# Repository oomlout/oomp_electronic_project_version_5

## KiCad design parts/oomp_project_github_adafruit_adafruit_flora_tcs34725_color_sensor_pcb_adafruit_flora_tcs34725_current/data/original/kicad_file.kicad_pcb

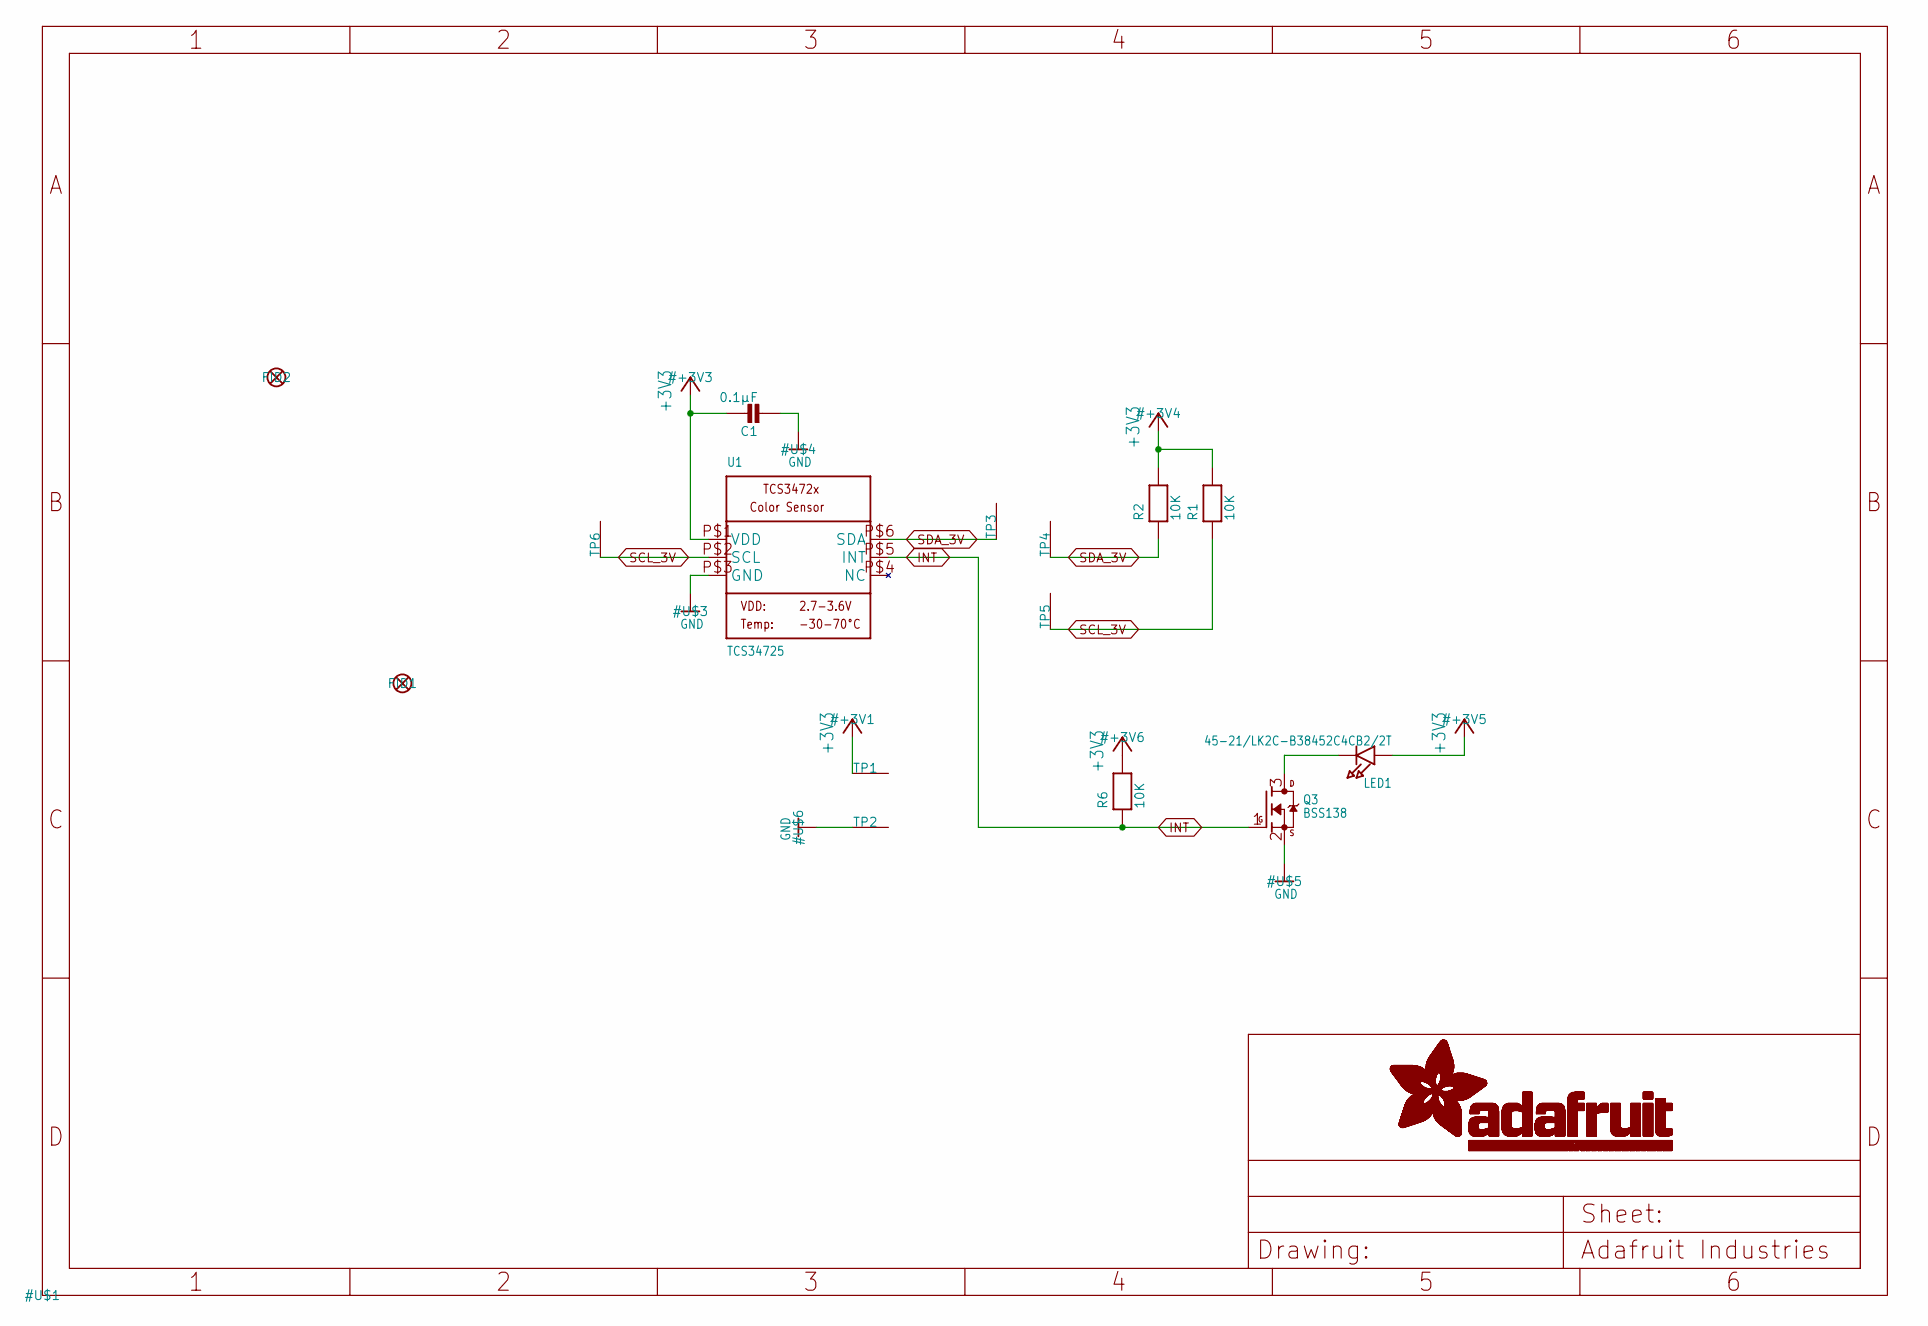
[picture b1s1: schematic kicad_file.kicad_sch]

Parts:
C1: 0.1µF; _0805
FID1, FID2: FIDUCIAL""; FIDUCIAL_1MM
LED1: 45-21/LK2C-B38452C4CB2/2T; EVERLIGHT_45-21
Q3: BSS138; SOT23-WIDE
R1, R2, R6: 10K; _0805
TP1, TP2, TP3, TP4, TP5, TP6: SEWTAP0.5IN; SEWINGTAP_0.5
U1: TCS34725; TCS3472_FN6

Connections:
+3V3: C1.1, LED1.A, R1.2, R2.2, R6.2, TP1.TAP, U1.P$1 (VDD)
GND: C1.2, Q3.2 (S), TP2.TAP, U1.P$3 (GND)
INT: Q3.1 (G), R6.1, U1.P$5 (INT)
unnamed: LED1.K (C), Q3.3 (D)
SCL_3V: R1.1, TP5.TAP, TP6.TAP, U1.P$2 (SCL)
SDA_3V: R2.1, TP3.TAP, TP4.TAP, U1.P$6 (SDA)

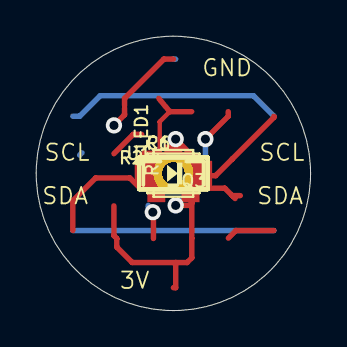
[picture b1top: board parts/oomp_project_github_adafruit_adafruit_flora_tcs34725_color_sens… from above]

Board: 2 copper layers, 15.2 x 15.2 mm, 16 parts (1 on the bottom side), 6 nets.

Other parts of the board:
U$8: ADAFRUIT_3.5MM

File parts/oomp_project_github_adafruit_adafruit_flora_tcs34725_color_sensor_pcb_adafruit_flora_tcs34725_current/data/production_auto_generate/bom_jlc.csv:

Comment,Designator,Footprint,LCSC Part #
,U$8,Adafruit Flora TCS34725-import-fps:ADAFRUIT_3.5MM,
0.1µF,C1,Adafruit Flora TCS34725-import-fps:_0805,
10K,"R1,R2,R6",Adafruit Flora TCS34725-import-fps:_0805,C17414
45-21/LK2C-B38452C4CB2/2T,LED1,Adafruit Flora TCS34725-import-fps:EVERLIGHT_45-21,
BSS138,Q3,Adafruit Flora TCS34725-import-fps:SOT23-WIDE,C52895
SEWTAP0.5IN,"TP1,TP2,TP3,TP4,TP5,TP6",Adafruit Flora TCS34725-import-fps:SEWINGTAP_0.5,
TCS34725,U1,Adafruit Flora TCS34725-import-fps:TCS3472_FN6,

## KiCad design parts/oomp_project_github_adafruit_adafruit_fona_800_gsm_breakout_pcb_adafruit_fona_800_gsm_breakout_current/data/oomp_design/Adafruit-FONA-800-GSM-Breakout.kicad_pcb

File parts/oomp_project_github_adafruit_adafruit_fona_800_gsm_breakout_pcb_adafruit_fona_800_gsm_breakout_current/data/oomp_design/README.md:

# OOMP KiCad design copy

Open `Adafruit-FONA-800-GSM-Breakout.kicad_pro` (or the `.kicad_pcb` / `.kicad_sch`) in KiCad. Local OOMP libraries are under `libraries/`. Original inputs are preserved in [../original/](../original/).

Only verified unchanged installed KiCad defaults were renamed. Modified, custom, unmatched and unavailable items remain unchanged. Soldering variants are never swapped during conversion. Existing pad coordinates, nets and UUIDs are preserved.

See [conversion_report.yaml](conversion_report.yaml) for every conversion and skip. Copy this directory before editing; regeneration refuses to overwrite edited design files.

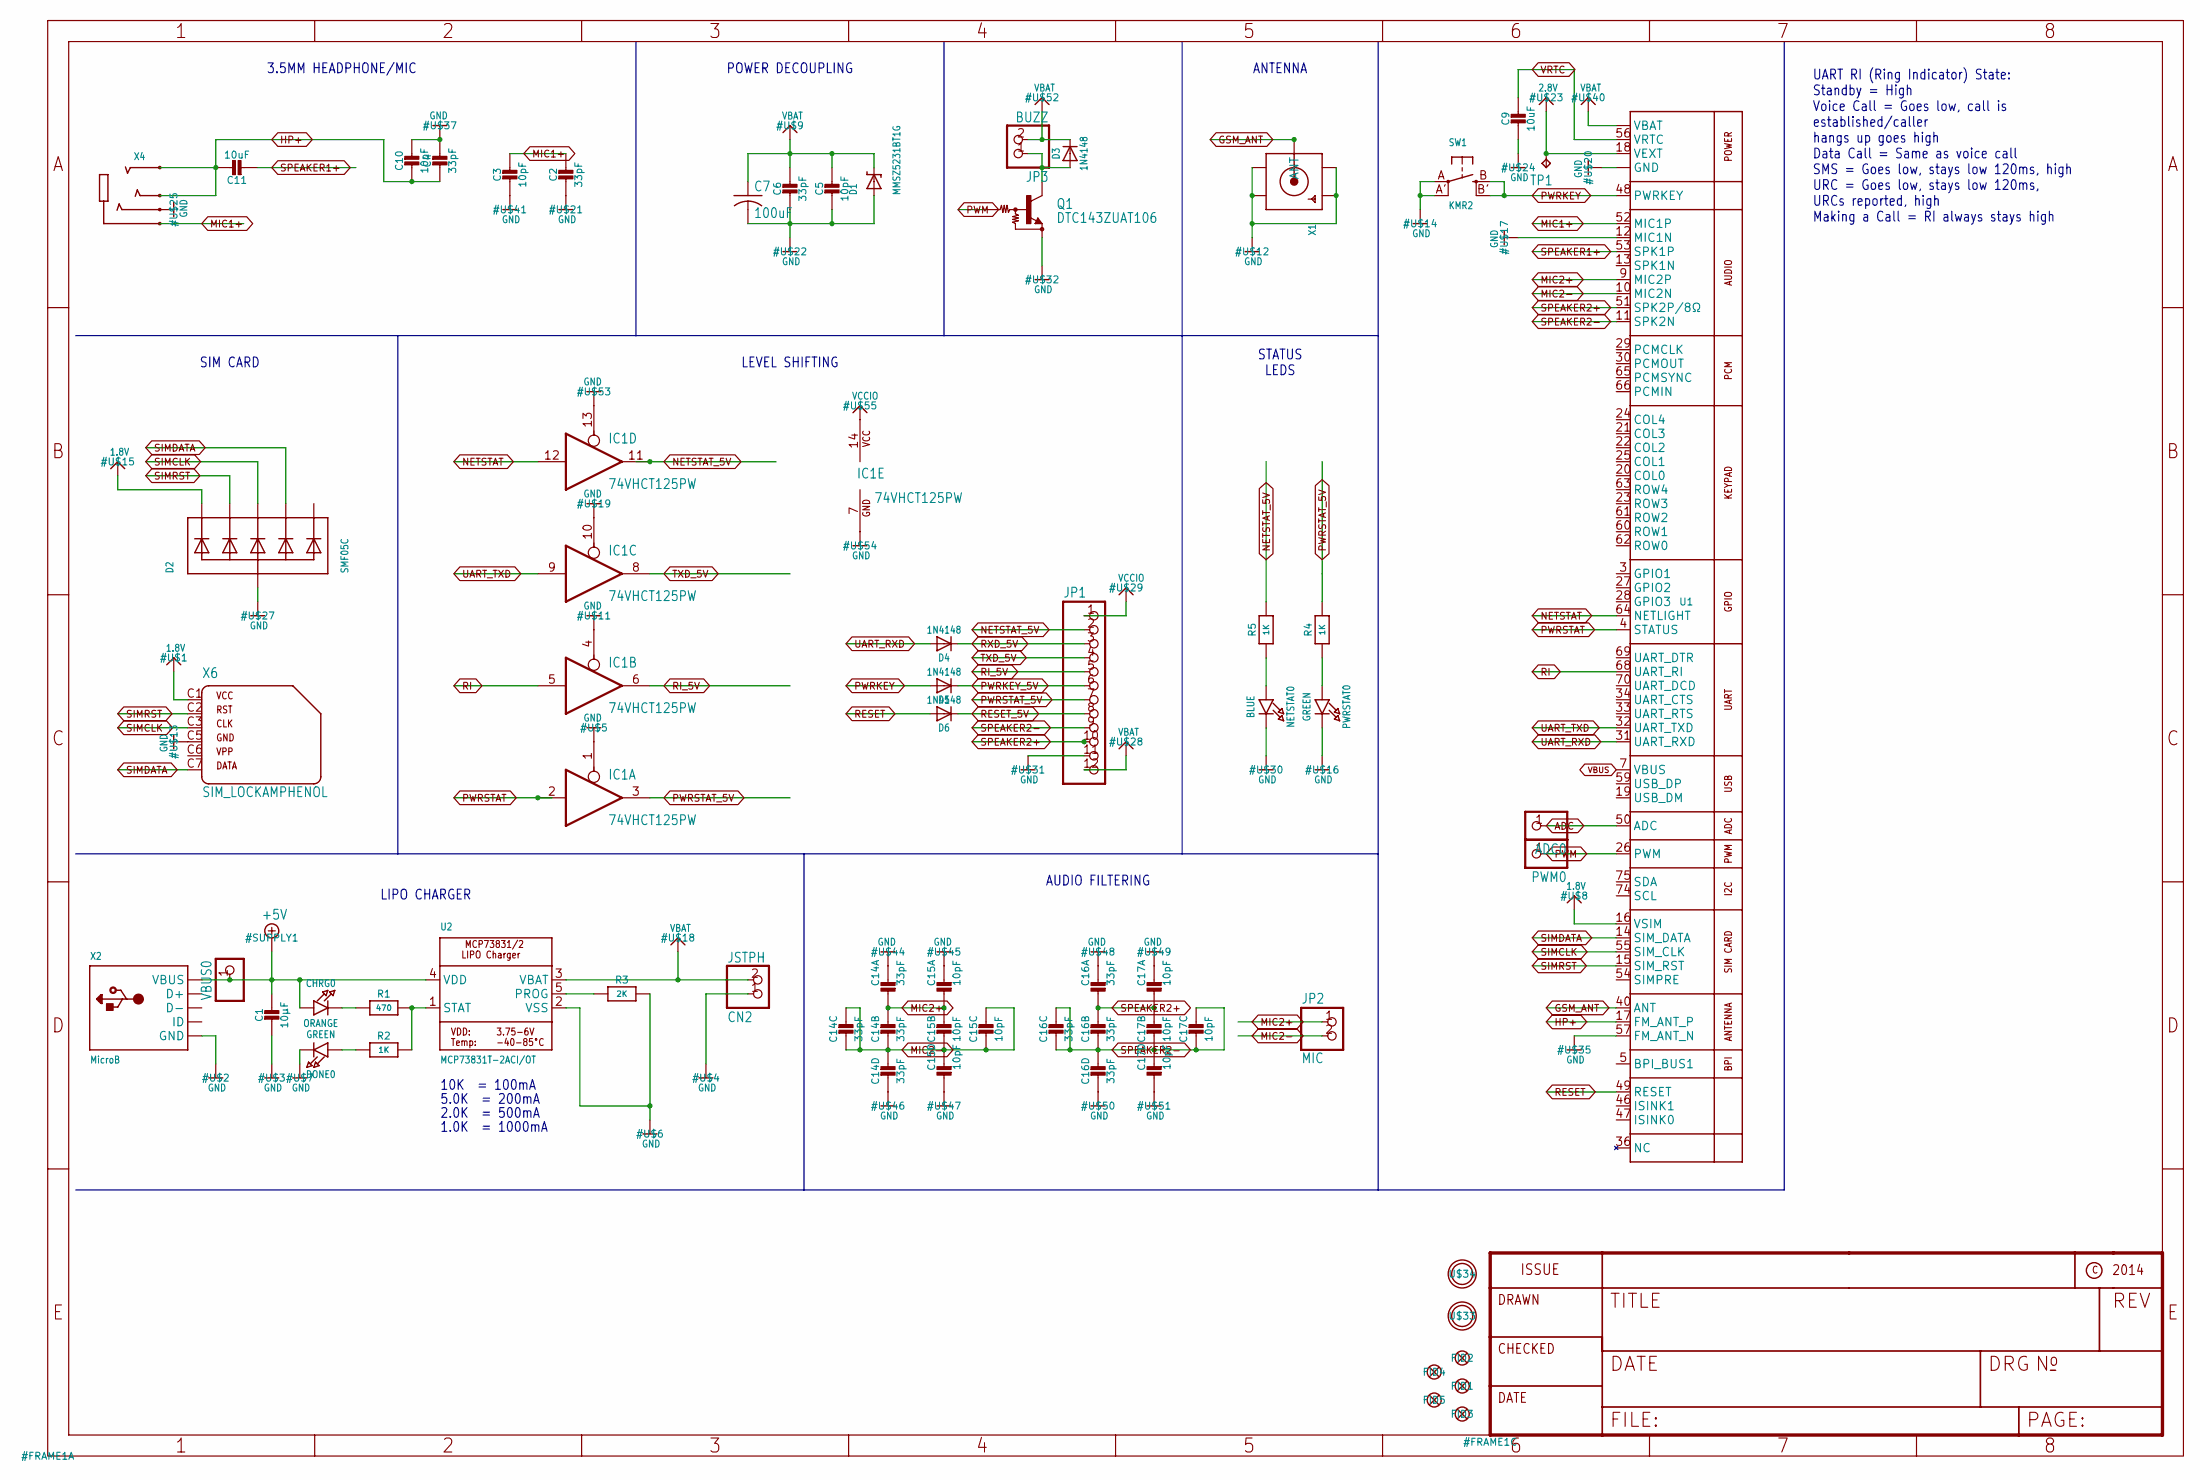
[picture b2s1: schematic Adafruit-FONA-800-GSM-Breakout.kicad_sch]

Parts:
ADC0: PINHD-1X1CB; 1X01-CLEANBIG
C1: 10µF; 0805-NO
C2, C4, C6: 33pF; 0805-NO
C3, C5, C10: 10pF; 0805-NO
C7: 100uF; C1210
C9, C11: 10uF; 0805-NO
C14, C16: 33pF; RESPACK_4X0603
C15, C17: 10pF; RESPACK_4X0603
CHRG0: ORANGE; CHIPLED_0805_NOOUTLINE
CN2: JSTPH; JSTPH2
D1: MMSZ5231BT1G; SOD-123
D2: SMF05C; SOT363
D3, D4, D5, D6: 1N4148; SOD-323
DONE0: GREEN; CHIPLED_0805_NOOUTLINE
FID1, FID2, FID3, FID4, FID5: FIDUCIAL""; FIDUCIAL_1MM
IC1: 74VHCT125PW; TSSOP14
JP1: PINHD-1X12-CB; 1X12-CB
JP2: MIC; 1X02_ROUND
JP3: BUZZ; 1X02_ROUND
NETSTAT0: BLUE; CHIPLED_0805_NOOUTLINE
PWM0: PINHD-1X1CB; 1X01-CLEANBIG
PWRSTAT0: GREEN; CHIPLED_0805_NOOUTLINE
Q1: DTC143ZUAT106; SC59-BEC
R1: 470; 0805-NO
R2, R4, R5: 1K; 0805-NO
R3: 2K; 0805-NO
SW1: KMR2; BTN_KMR2_4.6X2.8
TP1: TPTP11R; TP11R
U1: SIM800H/L; SIM800L
U2: MCP73831T-2ACI/OT; SOT23-5
U$33, U$34: MOUNTINGHOLE2.5; MOUNTINGHOLE_2.5_PLATED
VBUS0: PINHD-1X1CB; 1X01-CLEANBIG
X1: SMACONNECTOR_EDGE_UFL; SMA_EDGELAUNCH_UFL
X2: MicroB; 4UCONN_20329
X4: AUDIO_3.5MMJACK_4POL; 4UCONN_18510
X6: SIM_LOCKAMPHENOL; C707_10M006_512_2

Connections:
1.8V: D2.1 (C1), U1.16 (VSIM), X6.C1 (1)
2.8V: TP1.TP, U1.18 (VEXT)
+5V: C1.1, CHRG0.A, U2.4 (VDD), VBUS0.1, X2.VBUS
ADC: ADC0.1, U1.50 (ADC)
GND: C1.2, C2.2, C3.2, C4.1, C5.2, C6.2, C7.2, C9.2, C10.1, C14.5 (2), C14.8 (2), C15.4 (1), C15.8 (2), C16.5 (2), C16.8 (2), C17.4 (1), C17.8 (2), CN2.1, D1.A, D2.2 (A), DONE0.C, IC1.1 (OE), IC1.4 (OE), IC1.7 (GND), IC1.10 (OE), IC1.13 (OE), JP1.11, NETSTAT0.C, PWRSTAT0.C, Q1.E, R3.2, SW1.A, SW1.A' (P1), U1.2 (GND), U1.6 (GND), U1.8 (GND), U1.12 (MIC1N), U1.35 (GND), U1.37 (GND), U1.38 (GND), U1.39 (GND), U1.41 (GND), U1.43 (GND), U1.44 (GND), U1.45 (GND), U1.57 (FM_ANT_N), U1.58 (GND), U1.67 (GND), U1.71 (GND), U1.72 (GND), U1.73 (GND), U1.76 (GND), U1.77 (GND), U1.78 (GND), U1.79 (GND), U1.80 (GND), U1.81 (GND), U1.82 (GND), U1.83 (GND), U1.84 (GND), U1.85 (GND), U1.86 (GND), U1.87 (GND), U1.88 (GND), U2.2 (VSS), X1.GND@1 (GND1), X1.GND@2 (GND2), X1.GND@3 (GND3), X1.GND@4 (GND4), X2.BASE@1 (GND), X2.BASE@2 (GND), X2.GND, X2.SPRT@1 (GND), X2.SPRT@2 (GND), X2.SPRT@3 (GND), X2.SPRT@4 (GND), X4.4-INNER_SLEEVE (RING1), X6.C5 (4)
GSM_ANT: U1.40 (ANT), X1.P (ANT)
HP+: C4.2, C10.2, C11.1, U1.17 (FM_ANT_P), X4.2-TIP (RING3), X4.3-OUTER_SLEEVE (RING2)
MIC1+: C2.1, C3.1, U1.52 (MIC1P), X4.1-GND (TIP)
MIC2+: C14.1, C14.2 (1), C15.1, C15.2 (1), JP2.1, U1.9 (MIC2P)
MIC2-: C14.3 (1), C14.4 (1), C14.6 (2), C14.7 (2), C15.3 (1), C15.5 (2), C15.6 (2), C15.7 (2), JP2.2, U1.10 (MIC2N)
unnamed: CHRG0.C, R1.1
unnamed: R1.2, R2.2, U2.1 (STAT)
unnamed: PWRSTAT0.A, R4.1
unnamed: R3.1, U2.5 (PROG)
unnamed: DONE0.A, R2.1
unnamed: NETSTAT0.A, R5.1
unnamed: D3.A, JP3.1, Q1.C
NETSTAT: IC1.12 (I), U1.64 (NETLIGHT)
NETSTAT_5V: IC1.11 (O), JP1.2, R5.2
PWM: PWM0.1, Q1.B, U1.26 (PWM)
PWRKEY: D5.A, SW1.B (S), SW1.B' (S1), U1.48 (PWRKEY)
PWRKEY_5V: D5.C, JP1.6
PWRSTAT: IC1.2 (I), U1.4 (STATUS)
PWRSTAT_5V: IC1.3 (O), JP1.7, R4.2
RESET: D6.A, U1.49 (RESET)
RESET_5V: D6.C, JP1.8
RI: IC1.5 (I), U1.68 (UART_RI)
RI_5V: IC1.6 (O), JP1.5
RXD_5V: D4.C, JP1.3
SIMCLK: D2.4 (C3), U1.55 (SIM_CLK), X6.C3 (3)
SIMDATA: D2.5 (C4), U1.14 (SIM_DATA), X6.C7 (6)
SIMRST: D2.3 (C2), U1.15 (SIM_RST), X6.C2 (2)
SPEAKER1+: C11.2, U1.53 (SPK1P)
SPEAKER2+: C16.1, C16.2 (1), C17.1, C17.2 (1), JP1.10, U1.51 (SPK2P/8Ω)
SPEAKER2-: C16.3 (1), C16.4 (1), C16.6 (2), C16.7 (2), C17.3 (1), C17.5 (2), C17.6 (2), C17.7 (2), JP1.9, U1.11 (SPK2N)
TXD_5V: IC1.8 (O), JP1.4
UART_RXD: D4.A, U1.31 (UART_RXD)
UART_TXD: IC1.9 (I), U1.32 (UART_TXD)
VBAT: C5.1, C6.1, C7.1, CN2.2, D1.C, D3.C, JP1.12, JP3.2, U1.1 (VBAT), U1.42 (VBAT), U2.3 (VBAT)
VBUS: U1.7 (VBUS)
VCCIO: IC1.14 (VCC), JP1.1
VRTC: C9.1, U1.56 (VRTC)

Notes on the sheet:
AUDIO FILTERING
UART RI (Ring Indicator) State: Standby = High Voice Call = Goes low, call is established/caller hangs up goes high Data Call = Same as voice call SMS = Goes low, stays low 120ms, high URC = Goes low, stays low 120ms, URCs reported, high Making a Call = RI always stays high
2.0K = 500mA
10K = 100mA
LEVEL SHIFTING
1.0K = 1000mA
SIM CARD
LIPO CHARGER
ANTENNA
3.5MM HEADPHONE/MIC
STATUS LEDS
5.0K = 200mA
POWER DECOUPLING

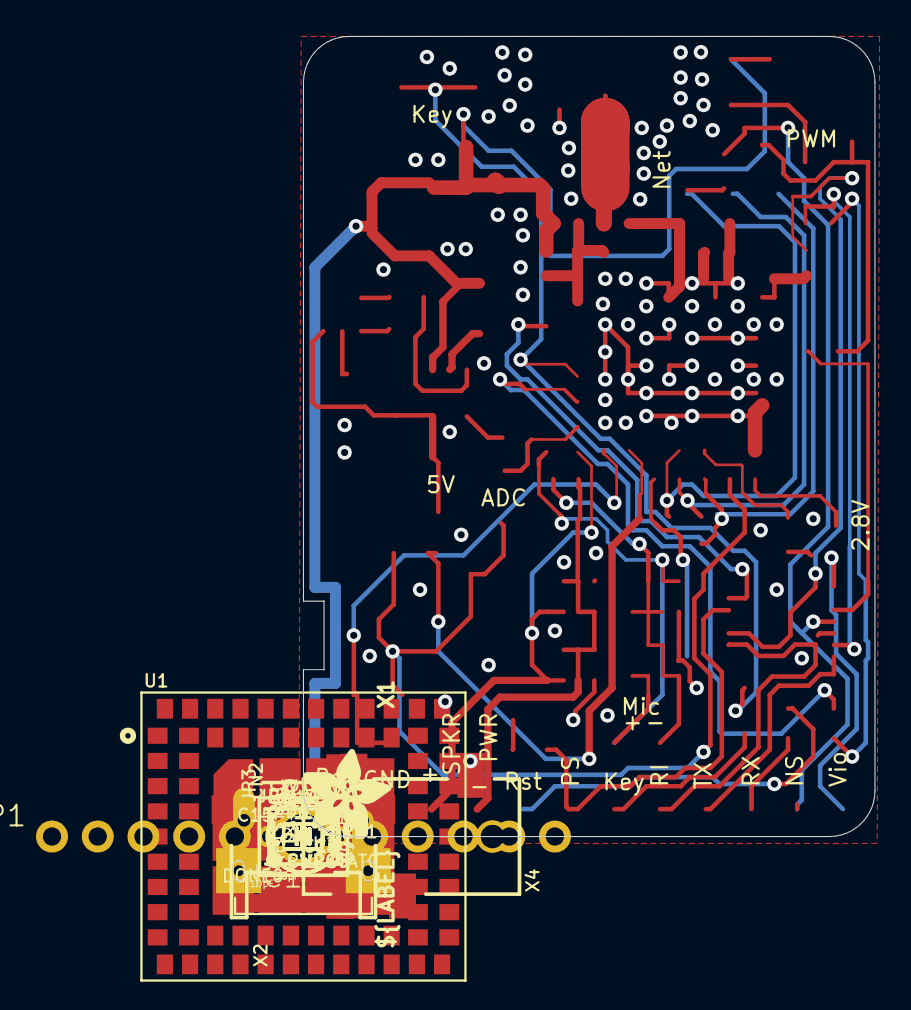
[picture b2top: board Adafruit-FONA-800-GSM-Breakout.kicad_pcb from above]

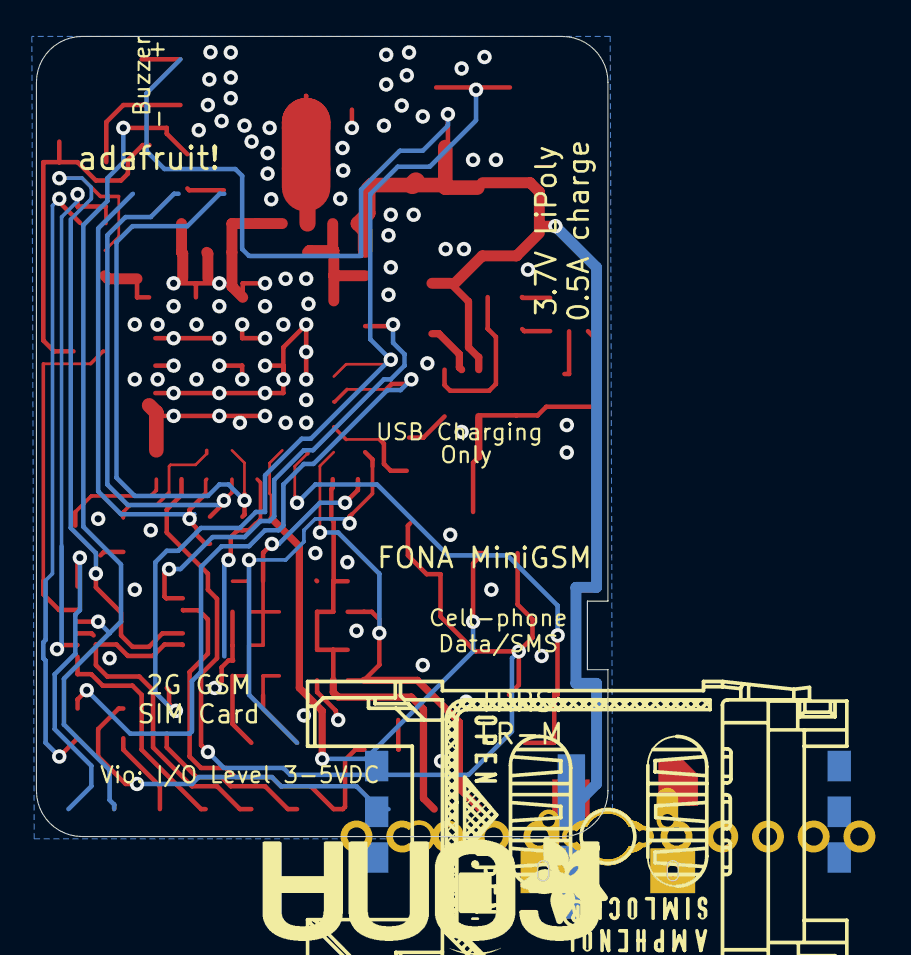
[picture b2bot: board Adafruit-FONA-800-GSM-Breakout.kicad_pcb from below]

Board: 2 copper layers, 31.8 x 44.5 mm, 56 parts (5 on the bottom side), 41 nets.

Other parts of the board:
U$10, U$36: ADAFRUIT_5MM
U$26: FONA_LOGO

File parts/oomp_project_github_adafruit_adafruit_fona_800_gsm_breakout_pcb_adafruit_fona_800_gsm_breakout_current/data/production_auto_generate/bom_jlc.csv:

Comment,Designator,Footprint,LCSC Part #
,"ADC0,PWM0,VBUS0",Adafruit-FONA-800-GSM-Breakout-import-fps:1X01-CLEANBIG,C7501259
,JP1,Adafruit-FONA-800-GSM-Breakout-import-fps:1X12-CB,C7501588
,X4,Adafruit-FONA-800-GSM-Breakout-import-fps:4UCONN_18510,
,"U$10,U$36",Adafruit-FONA-800-GSM-Breakout-import-fps:ADAFRUIT_5MM,
,U$26,Adafruit-FONA-800-GSM-Breakout-import-fps:FONA_LOGO,
,X1,Adafruit-FONA-800-GSM-Breakout-import-fps:SMA_EDGELAUNCH_UFL,
100uF,C7,Adafruit-FONA-800-GSM-Breakout-import-fps:C1210,
10pF,"C3,C5,C10",Adafruit-FONA-800-GSM-Breakout-import-fps:0805-NO,
10pF,"C15,C17",Adafruit-FONA-800-GSM-Breakout-import-fps:RESPACK_4X0603,
10uF,"C9,C11",Adafruit-FONA-800-GSM-Breakout-import-fps:0805-NO,
10µF,C1,Adafruit-FONA-800-GSM-Breakout-import-fps:0805-NO,
1K,"R2,R4,R5",Adafruit-FONA-800-GSM-Breakout-import-fps:0805-NO,C17513
1N4148,"D3,D4,D5,D6",Adafruit-FONA-800-GSM-Breakout-import-fps:SOD-323,
2K,R3,Adafruit-FONA-800-GSM-Breakout-import-fps:0805-NO,C17604
33pF,"C2,C4,C6",Adafruit-FONA-800-GSM-Breakout-import-fps:0805-NO,
33pF,"C14,C16",Adafruit-FONA-800-GSM-Breakout-import-fps:RESPACK_4X0603,C107047
470,R1,Adafruit-FONA-800-GSM-Breakout-import-fps:0805-NO,C17710
74VHCT125PW,IC1,Adafruit-FONA-800-GSM-Breakout-import-fps:TSSOP14,
BLUE,NETSTAT0,Adafruit-FONA-800-GSM-Breakout-import-fps:CHIPLED_0805_NOOUTLINE,
BUZZ,JP3,Adafruit-FONA-800-GSM-Breakout-import-fps:1X02_ROUND,C492401
DTC143ZUAT106,Q1,Adafruit-FONA-800-GSM-Breakout-import-fps:SC59-BEC,
GREEN,"DONE0,PWRSTAT0",Adafruit-FONA-800-GSM-Breakout-import-fps:CHIPLED_0805_NOOUTLINE,
JSTPH,CN2,Adafruit-FONA-800-GSM-Breakout-import-fps:JSTPH2,
KMR2,SW1,Adafruit-FONA-800-GSM-Breakout-import-fps:BTN_KMR2_4.6X2.8,
MCP73831T-2ACI/OT,U2,Adafruit-FONA-800-GSM-Breakout-import-fps:SOT23-5,
MIC,JP2,Adafruit-FONA-800-GSM-Breakout-import-fps:1X02_ROUND,C492401
MicroB,X2,Adafruit-FONA-800-GSM-Breakout-import-fps:4UCONN_20329,
MMSZ5231BT1G,D1,Adafruit-FONA-800-GSM-Breakout-import-fps:SOD-123,
ORANGE,CHRG0,Adafruit-FONA-800-GSM-Breakout-import-fps:CHIPLED_0805_NOOUTLINE,
SIM800H/L,U1,Adafruit-FONA-800-GSM-Breakout-import-fps:SIM800L,
SIM_LOCKAMPHENOL,X6,Adafruit-FONA-800-GSM-Breakout-import-fps:C707_10M006_512_2,
SMF05C,D2,Adafruit-FONA-800-GSM-Breakout-import-fps:SOT363,
TPTP11R,TP1,Adafruit-FONA-800-GSM-Breakout-import-fps:TP11R,

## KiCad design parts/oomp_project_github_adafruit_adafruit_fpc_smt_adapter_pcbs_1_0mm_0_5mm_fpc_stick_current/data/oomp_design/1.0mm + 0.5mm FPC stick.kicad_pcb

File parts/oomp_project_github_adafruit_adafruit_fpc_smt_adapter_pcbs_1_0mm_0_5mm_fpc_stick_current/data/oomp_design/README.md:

# OOMP KiCad design copy

Open `1.0mm + 0.5mm FPC stick.kicad_pro` (or the `.kicad_pcb` / `.kicad_sch`) in KiCad. Local OOMP libraries are under `libraries/`. Original inputs are preserved in [../original/](../original/).

Only verified unchanged installed KiCad defaults were renamed. Modified, custom, unmatched and unavailable items remain unchanged. Soldering variants are never swapped during conversion. Existing pad coordinates, nets and UUIDs are preserved.

See [conversion_report.yaml](conversion_report.yaml) for every conversion and skip. Copy this directory before editing; regeneration refuses to overwrite edited design files.

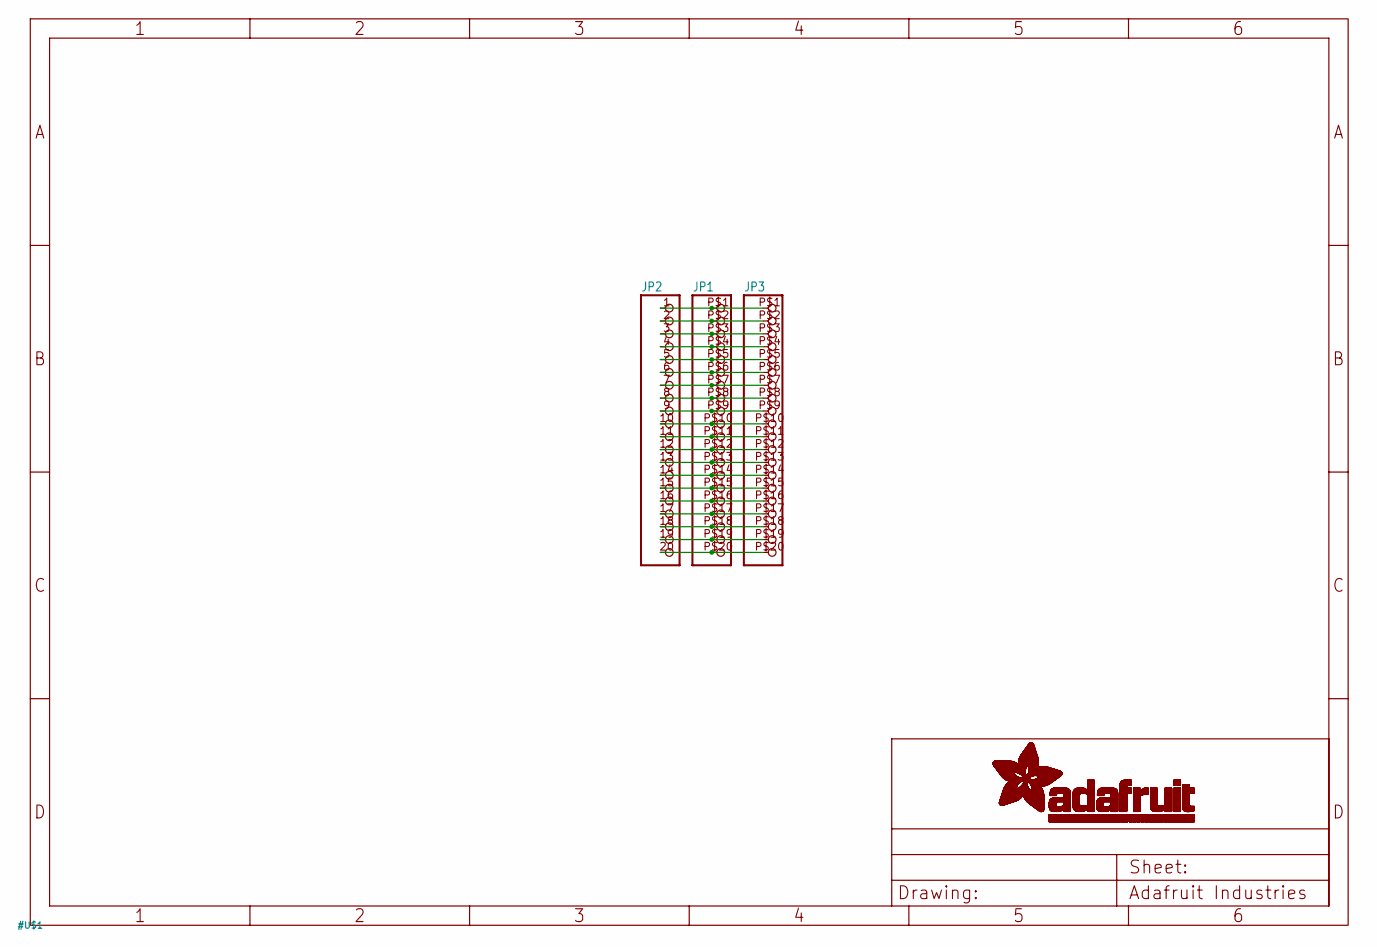
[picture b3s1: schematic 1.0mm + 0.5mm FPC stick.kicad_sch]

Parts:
JP1: HEADER-1X20FPC_1.0MM; FPC_GENERIC_1.0MM_20PIN
JP2: HEADER-1X20ROUND; 1X20_ROUND
JP3: HEADER-1X20FPC_0.5MM; FPC_GENERIC_0.5MM_20PIN

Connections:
unnamed: JP1.P$1 (1), JP2.1, JP3.P$1 (1)
unnamed: JP1.P$2 (2), JP2.2, JP3.P$2 (2)
unnamed: JP1.P$3 (3), JP2.3, JP3.P$3 (3)
unnamed: JP1.P$4 (4), JP2.4, JP3.P$4 (4)
unnamed: JP1.P$5 (5), JP2.5, JP3.P$5 (5)
unnamed: JP1.P$6 (6), JP2.6, JP3.P$6 (6)
unnamed: JP1.P$7 (7), JP2.7, JP3.P$7 (7)
unnamed: JP1.P$8 (8), JP2.8, JP3.P$8 (8)
unnamed: JP1.P$9 (9), JP2.9, JP3.P$9 (9)
unnamed: JP1.P$10 (10), JP2.10, JP3.P$10 (10)
unnamed: JP1.P$11 (11), JP2.11, JP3.P$11 (11)
unnamed: JP1.P$12 (12), JP2.12, JP3.P$12 (12)
unnamed: JP1.P$13 (13), JP2.13, JP3.P$13 (13)
unnamed: JP1.P$14 (14), JP2.14, JP3.P$14 (14)
unnamed: JP1.P$15 (15), JP2.15, JP3.P$15 (15)
unnamed: JP1.P$16 (16), JP2.16, JP3.P$16 (16)
unnamed: JP1.P$17 (17), JP2.17, JP3.P$17 (17)
unnamed: JP1.P$18 (18), JP2.18, JP3.P$18 (18)
unnamed: JP1.P$19 (19), JP2.19, JP3.P$19 (19)
unnamed: JP1.P$20 (20), JP2.20, JP3.P$20 (20)

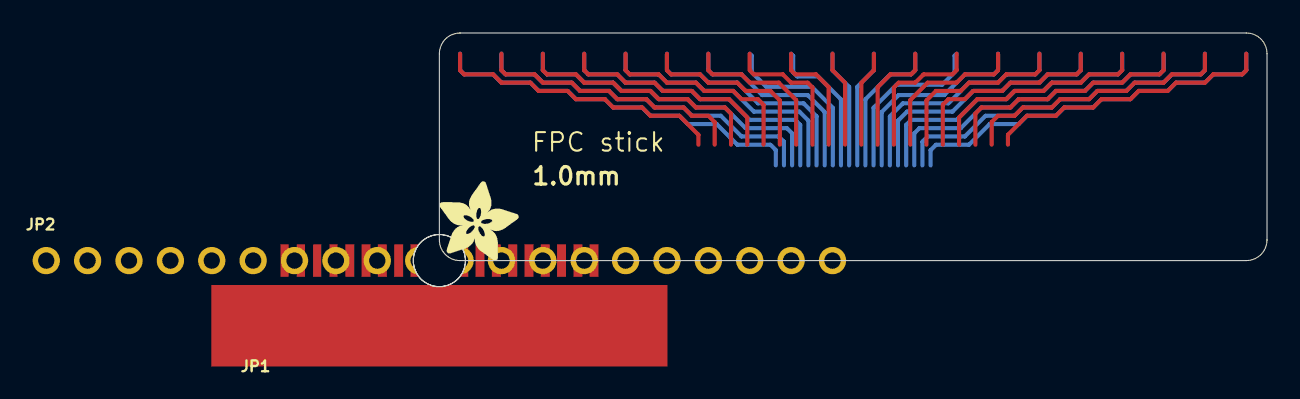
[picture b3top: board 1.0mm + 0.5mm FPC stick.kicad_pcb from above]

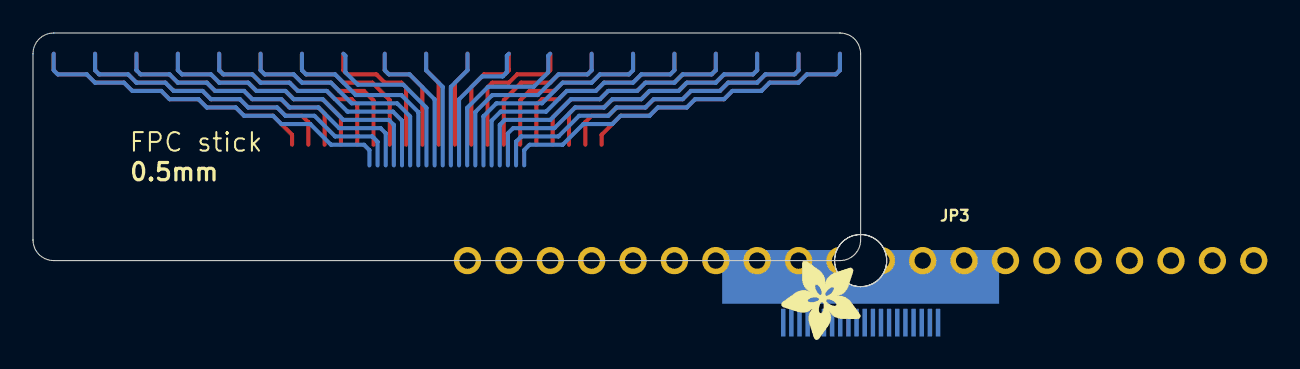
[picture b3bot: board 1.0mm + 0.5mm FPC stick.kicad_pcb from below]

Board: 2 copper layers, 50.8 x 14.0 mm, 7 parts (2 on the bottom side), 20 nets.

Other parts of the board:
U$2, U$3: ADAFRUIT_5MM
UNK_HOLE_0: dummyfp0
UNK_HOLE_1: dummyfp1

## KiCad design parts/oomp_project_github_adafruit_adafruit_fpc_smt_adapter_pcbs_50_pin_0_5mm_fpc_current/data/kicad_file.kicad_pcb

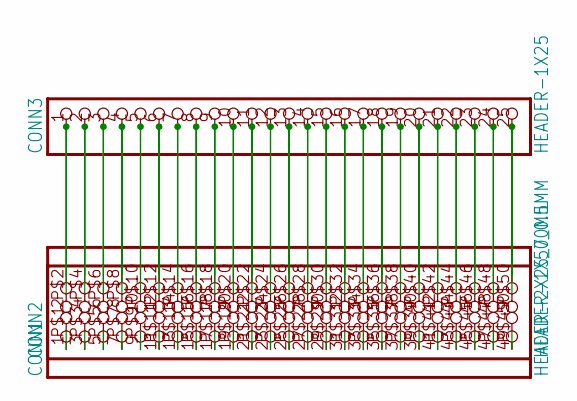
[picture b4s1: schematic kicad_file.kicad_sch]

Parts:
CONN1: HEADER-2X25_70MIL; 2X25
CONN2: HEADER-1X50_0.5MM; FPC_GENERIC_0.5MM_50PIN
CONN3: HEADER-1X25; 1X25_ROUND_70MIL

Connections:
unnamed: CONN1.1, CONN2.P$1 (1)
unnamed: CONN1.2, CONN2.P$2 (2), CONN3.1
unnamed: CONN1.3, CONN2.P$3 (3)
unnamed: CONN1.4, CONN2.P$4 (4), CONN3.2
unnamed: CONN1.5, CONN2.P$5 (5)
unnamed: CONN1.6, CONN2.P$6 (6), CONN3.3
unnamed: CONN1.7, CONN2.P$7 (7)
unnamed: CONN1.8, CONN2.P$8 (8), CONN3.4
unnamed: CONN1.9, CONN2.P$9 (9)
unnamed: CONN1.10, CONN2.P$10 (10), CONN3.5
unnamed: CONN1.11, CONN2.P$11 (11)
unnamed: CONN1.12, CONN2.P$12 (12), CONN3.6
unnamed: CONN1.13, CONN2.P$13 (13)
unnamed: CONN1.14, CONN2.P$14 (14), CONN3.7
unnamed: CONN1.15, CONN2.P$15 (15)
unnamed: CONN1.16, CONN2.P$16 (16), CONN3.8
unnamed: CONN1.17, CONN2.P$17 (17)
unnamed: CONN1.18, CONN2.P$18 (18), CONN3.9
unnamed: CONN1.19, CONN2.P$19 (19)
unnamed: CONN1.20, CONN2.P$20 (20), CONN3.10
unnamed: CONN1.21, CONN2.P$21 (21)
unnamed: CONN1.22, CONN2.P$22 (22), CONN3.11
unnamed: CONN1.23, CONN2.P$23 (23)
unnamed: CONN1.24, CONN2.P$24 (24), CONN3.12
unnamed: CONN1.25, CONN2.P$25 (25)
unnamed: CONN1.26, CONN2.P$26 (26), CONN3.13
unnamed: CONN1.27, CONN2.P$27 (27)
unnamed: CONN1.28, CONN2.P$28 (28), CONN3.14
unnamed: CONN1.29, CONN2.P$29 (29)
unnamed: CONN1.30, CONN2.P$30 (30), CONN3.15
unnamed: CONN1.31, CONN2.P$31 (31)
unnamed: CONN1.32, CONN2.P$32 (32), CONN3.16
unnamed: CONN1.33, CONN2.P$33 (33)
unnamed: CONN1.34, CONN2.P$34 (34), CONN3.17
unnamed: CONN1.35, CONN2.P$35 (35)
unnamed: CONN1.36, CONN2.P$36 (36), CONN3.18
unnamed: CONN1.37, CONN2.P$37 (37)
unnamed: CONN1.38, CONN2.P$38 (38), CONN3.19
unnamed: CONN1.39, CONN2.P$39 (39)
unnamed: CONN1.40, CONN2.P$40 (40), CONN3.20
unnamed: CONN1.41, CONN2.P$41 (41)
unnamed: CONN1.42, CONN2.P$42 (42), CONN3.21
unnamed: CONN1.43, CONN2.P$43 (43)
unnamed: CONN1.44, CONN2.P$44 (44), CONN3.22
unnamed: CONN1.45, CONN2.P$45 (45)
unnamed: CONN1.46, CONN2.P$46 (46), CONN3.23
unnamed: CONN1.47, CONN2.P$47 (47)
unnamed: CONN1.48, CONN2.P$48 (48), CONN3.24
unnamed: CONN1.49, CONN2.P$49 (49)
unnamed: CONN1.50, CONN2.P$50 (50), CONN3.25

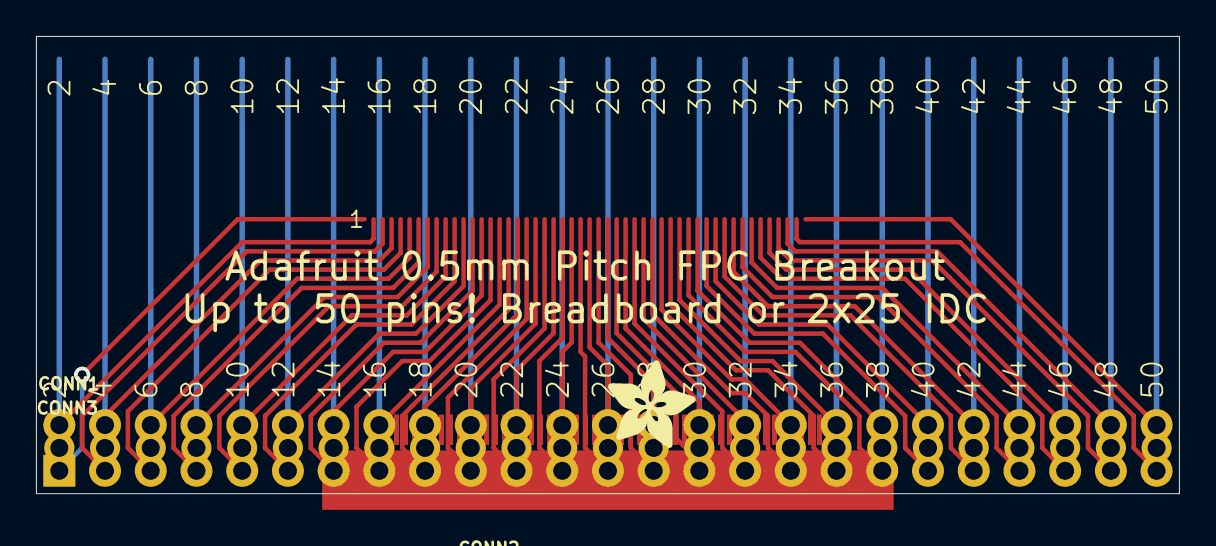
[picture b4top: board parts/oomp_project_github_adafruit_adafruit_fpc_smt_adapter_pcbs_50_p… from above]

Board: 2 copper layers, 63.5 x 25.4 mm, 4 parts (0 on the bottom side), 50 nets.

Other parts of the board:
U$1: ADAFRUIT_5MM

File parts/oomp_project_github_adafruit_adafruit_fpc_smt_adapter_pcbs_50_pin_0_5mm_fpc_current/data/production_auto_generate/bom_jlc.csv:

Comment,Designator,Footprint,LCSC Part #
,U$1,50 pin 0.5mm FPC-import-fps:ADAFRUIT_5MM,
HEADER-1X25,CONN3,50 pin 0.5mm FPC-import-fps:1X25_ROUND_70MIL,C2883713
HEADER-1X50_0.5MM,CONN2,50 pin 0.5mm FPC-import-fps:FPC_GENERIC_0.5MM_50PIN,
HEADER-2X25_70MIL,CONN1,50 pin 0.5mm FPC-import-fps:2X25,

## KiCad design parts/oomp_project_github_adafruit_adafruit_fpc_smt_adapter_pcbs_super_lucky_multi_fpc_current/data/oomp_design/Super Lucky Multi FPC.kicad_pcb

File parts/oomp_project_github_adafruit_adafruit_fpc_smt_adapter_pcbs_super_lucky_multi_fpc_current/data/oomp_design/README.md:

# OOMP KiCad design copy

Open `Super Lucky Multi FPC.kicad_pro` (or the `.kicad_pcb` / `.kicad_sch`) in KiCad. Local OOMP libraries are under `libraries/`. Original inputs are preserved in [../original/](../original/).

Only verified unchanged installed KiCad defaults were renamed. Modified, custom, unmatched and unavailable items remain unchanged. Soldering variants are never swapped during conversion. Existing pad coordinates, nets and UUIDs are preserved.

See [conversion_report.yaml](conversion_report.yaml) for every conversion and skip. Copy this directory before editing; regeneration refuses to overwrite edited design files.

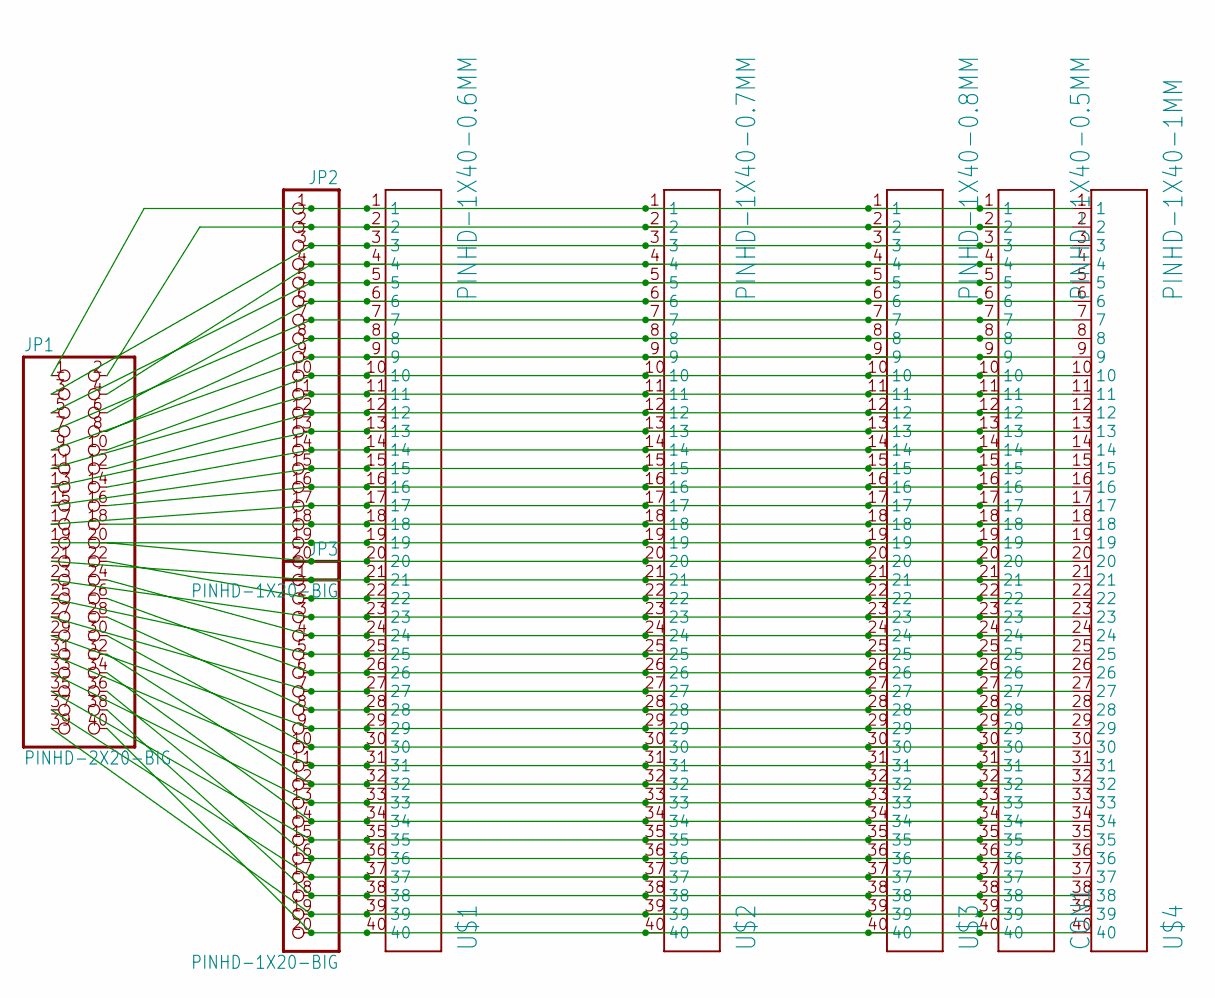
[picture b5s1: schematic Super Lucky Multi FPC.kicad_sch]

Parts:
CON1: PINHD-1X40-0.5MM; 1X40-0.5MM
JP1: PINHD-2X20-BIG; 2X20-BIG
JP2, JP3: PINHD-1X20-BIG; 1X20-BIG
U$1: PINHD-1X40-0.6MM; 1X40-0.6MM
U$2: PINHD-1X40-0.7MM; 1X40-0.7MM
U$3: PINHD-1X40-0.8MM; 1X40-0.8MM
U$4: PINHD-1X40-1MM; 1X40-1MM

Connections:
unnamed: CON1.1, JP1.1, JP2.1, U$1.1, U$2.1, U$3.1, U$4.1
unnamed: CON1.2, JP1.2, JP2.2, U$1.2, U$2.2, U$3.2, U$4.2
unnamed: CON1.3, JP1.3, JP2.3, U$1.3, U$2.3, U$3.3, U$4.3
unnamed: CON1.4, JP1.4, JP2.4, U$1.4, U$2.4, U$3.4, U$4.4
unnamed: CON1.5, JP1.5, JP2.5, U$1.5, U$2.5, U$3.5, U$4.5
unnamed: CON1.6, JP1.6, JP2.6, U$1.6, U$2.6, U$3.6, U$4.6
unnamed: CON1.7, JP1.7, JP2.7, U$1.7, U$2.7, U$3.7, U$4.7
unnamed: CON1.8, JP1.8, JP2.8, U$1.8, U$2.8, U$3.8, U$4.8
unnamed: CON1.9, JP1.9, JP2.9, U$1.9, U$2.9, U$3.9, U$4.9
unnamed: CON1.10, JP1.10, JP2.10, U$1.10, U$2.10, U$3.10, U$4.10
unnamed: CON1.11, JP1.11, JP2.11, U$1.11, U$2.11, U$3.11, U$4.11
unnamed: CON1.12, JP1.12, JP2.12, U$1.12, U$2.12, U$3.12, U$4.12
unnamed: CON1.13, JP1.13, JP2.13, U$1.13, U$2.13, U$3.13, U$4.13
unnamed: CON1.14, JP1.14, JP2.14, U$1.14, U$2.14, U$3.14, U$4.14
unnamed: CON1.15, JP1.15, JP2.15, U$1.15, U$2.15, U$3.15, U$4.15
unnamed: CON1.16, JP1.16, JP2.16, U$1.16, U$2.16, U$3.16, U$4.16
unnamed: CON1.17, JP1.17, JP2.17, U$1.17, U$2.17, U$3.17, U$4.17
unnamed: CON1.18, JP1.18, JP2.18, U$1.18, U$2.18, U$3.18, U$4.18
unnamed: CON1.19, JP1.19, JP2.19, U$1.19, U$2.19, U$3.19, U$4.19
unnamed: CON1.20, JP1.20, JP2.20, U$1.20, U$2.20, U$3.20, U$4.20
unnamed: CON1.21, JP1.21, JP3.1, U$1.21, U$2.21, U$3.21, U$4.21
unnamed: CON1.22, JP1.22, JP3.2, U$1.22, U$2.22, U$3.22, U$4.22
unnamed: CON1.23, JP1.23, JP3.3, U$1.23, U$2.23, U$3.23, U$4.23
unnamed: CON1.24, JP1.24, JP3.4, U$1.24, U$2.24, U$3.24, U$4.24
unnamed: CON1.25, JP1.25, JP3.5, U$1.25, U$2.25, U$3.25, U$4.25
unnamed: CON1.26, JP1.26, JP3.6, U$1.26, U$2.26, U$3.26, U$4.26
unnamed: CON1.27, JP1.27, JP3.7, U$1.27, U$2.27, U$3.27, U$4.27
unnamed: CON1.28, JP1.28, JP3.8, U$1.28, U$2.28, U$3.28, U$4.28
unnamed: CON1.29, JP1.29, JP3.9, U$1.29, U$2.29, U$3.29, U$4.29
unnamed: CON1.30, JP1.30, JP3.10, U$1.30, U$2.30, U$3.30, U$4.30
unnamed: CON1.31, JP1.31, JP3.11, U$1.31, U$2.31, U$3.31, U$4.31
unnamed: CON1.32, JP1.32, JP3.12, U$1.32, U$2.32, U$3.32, U$4.32
unnamed: CON1.33, JP1.33, JP3.13, U$1.33, U$2.33, U$3.33, U$4.33
unnamed: CON1.34, JP1.34, JP3.14, U$1.34, U$2.34, U$3.34, U$4.34
unnamed: CON1.35, JP1.35, JP3.15, U$1.35, U$2.35, U$3.35, U$4.35
unnamed: CON1.36, JP1.36, JP3.16, U$1.36, U$2.36, U$3.36, U$4.36
unnamed: CON1.37, JP1.37, JP3.17, U$1.37, U$2.37, U$3.37, U$4.37
unnamed: CON1.38, JP1.38, JP3.18, U$1.38, U$2.38, U$3.38, U$4.38
unnamed: CON1.39, JP1.39, JP3.19, U$1.39, U$2.39, U$3.39, U$4.39
unnamed: CON1.40, JP1.40, JP3.20, U$1.40, U$2.40, U$3.40, U$4.40
